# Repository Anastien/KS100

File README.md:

# KS100
KS100 is my take on entry level scientific calculators.

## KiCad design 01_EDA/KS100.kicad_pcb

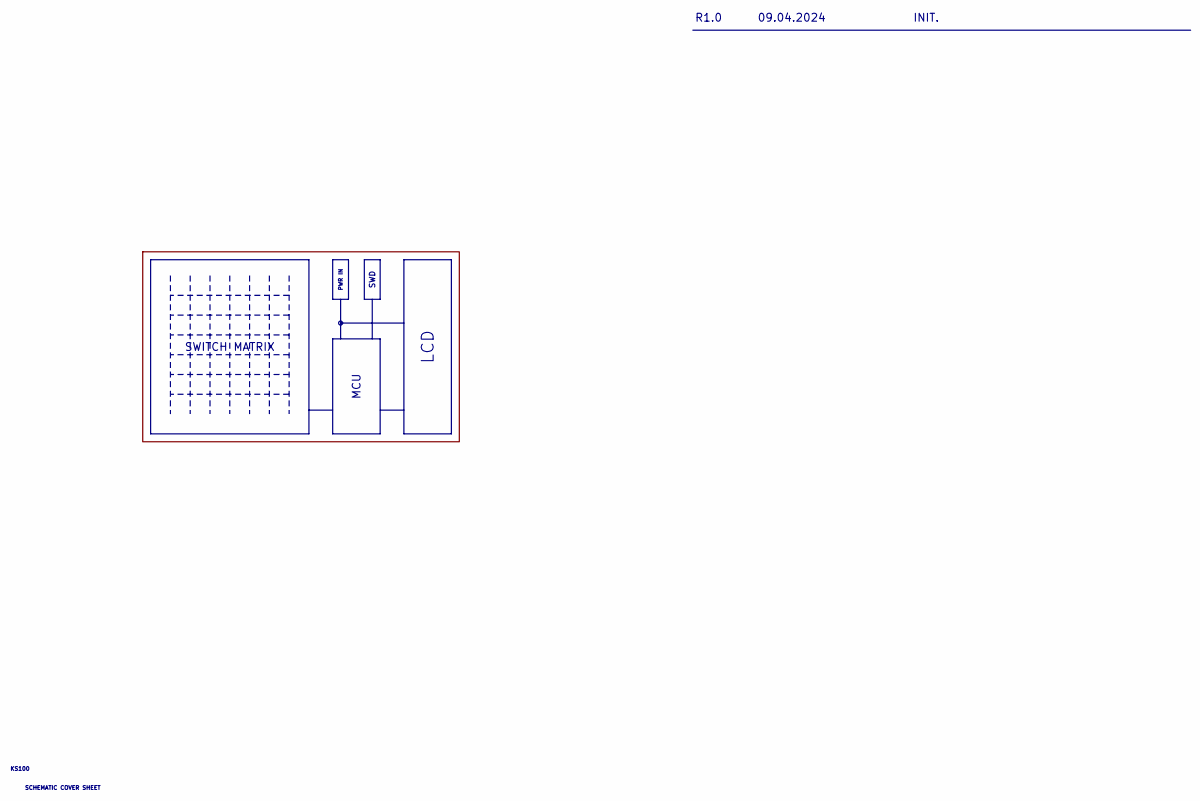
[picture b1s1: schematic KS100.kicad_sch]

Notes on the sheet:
R1.0
SCHEMATIC COVER SHEET
INIT.
09.04.2024
KS100
LCD
SWITCH MATRIX
SWD
MCU
PWR IN

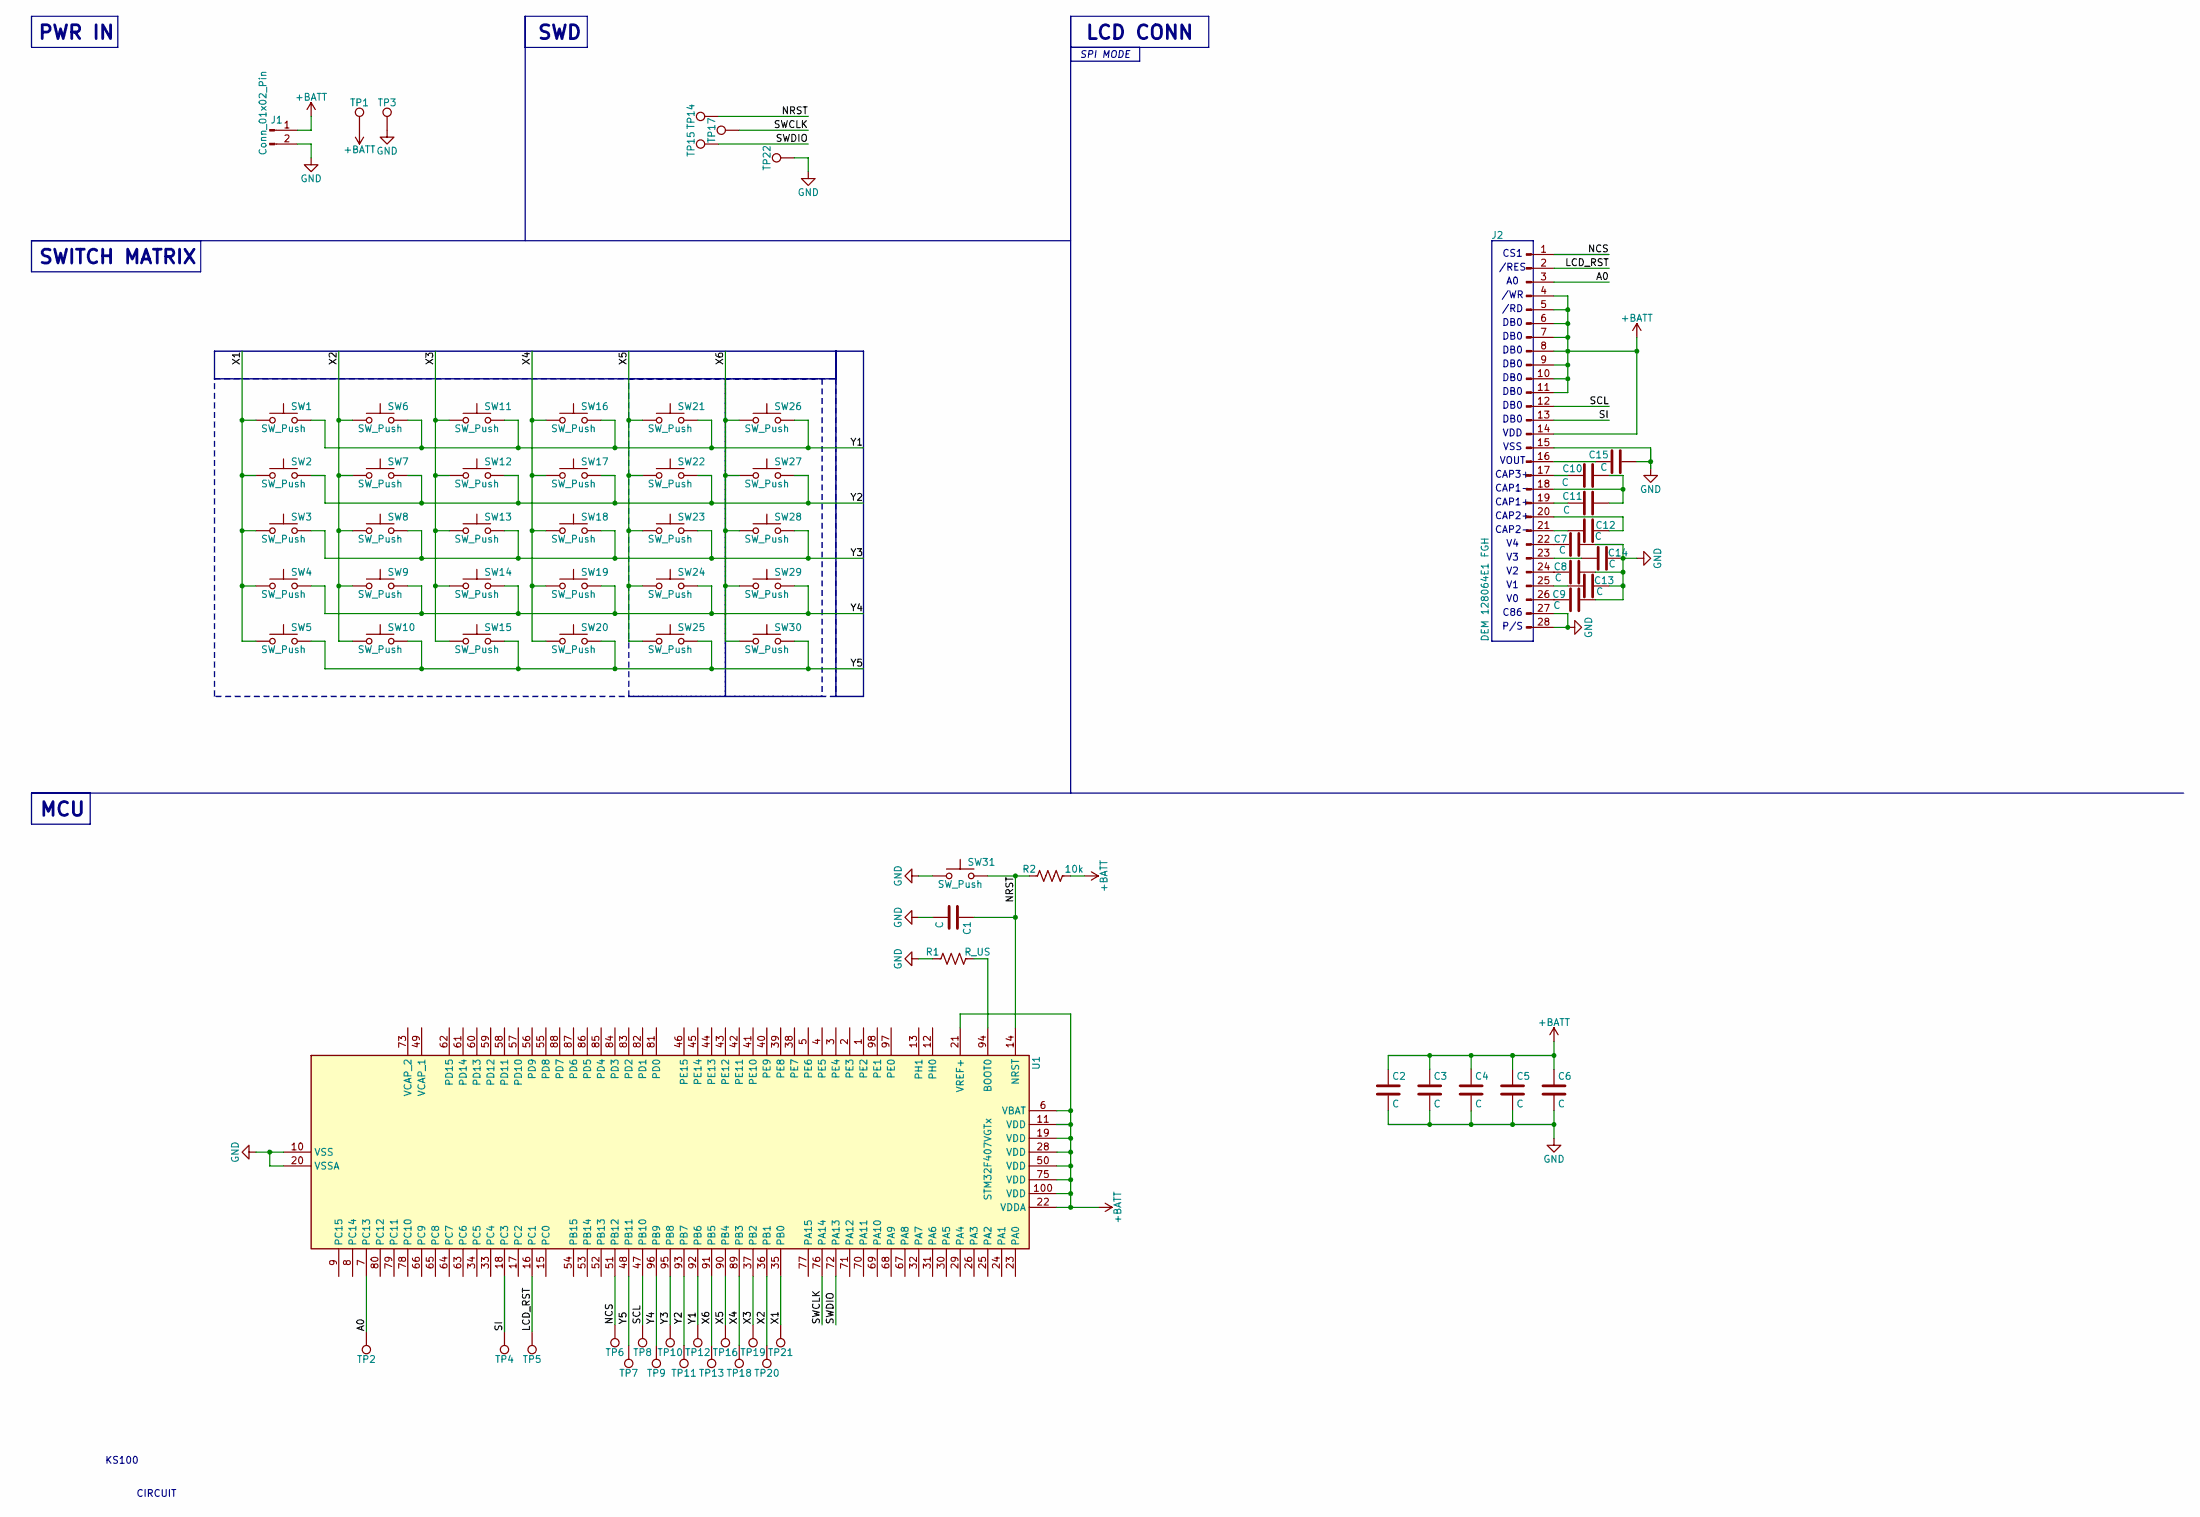
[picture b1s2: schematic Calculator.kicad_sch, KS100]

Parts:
C1, C2, C3, C4, C5, C6, C7, C8, C9, C10, C11, C12, C13, C14, C15: C; C_0603_1608Metric_Pad1.08x0.95mm_HandSolder
J1: Conn_01x02_Pin; JST_VH_B2P-VH-B_1x02_P3.96mm_Vertical
J2: DEM 128064E1 FGH
R1: R_US; R_0603_1608Metric_Pad0.98x0.95mm_HandSolder
R2: 10k; R_0603_1608Metric_Pad0.98x0.95mm_HandSolder
SW1, SW2, SW3, SW4, SW5, SW6, SW7, SW8, SW9, SW10, SW11, SW12, SW13, SW14, SW15, SW16, SW17, SW18, SW19, SW20, SW21, SW22, SW23, SW24, SW25, SW26, SW27, SW28, SW29, SW30, SW31: SW_Push; SW_PUSH_1P1T_6x3.5mm_H4.3_APEM_MJTP1243
TP1, TP2, TP3, TP4, TP5, TP6, TP7, TP8, TP9, TP10, TP11, TP12, TP13, TP16, TP18, TP19, TP20, TP21: TestPoint; TestPoint_THTPad_1.0x1.0mm_Drill0.5mm
TP14, TP15, TP17, TP22: TestPoint; TestPoint_THTPad_2.0x2.0mm_Drill1.0mm
U1: STM32F407VGTx; LQFP-100_14x14mm_P0.5mm

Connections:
+BATT: C2.1, C3.1, C4.1, C5.1, C6.1, J1.1, J2.4, J2.5, J2.6, J2.7, J2.8, J2.9, J2.10, J2.11, J2.14, R2.1, TP1.1, U1.6 (VBAT), U1.11 (VDD), U1.19 (VDD), U1.21 (VREF+), U1.22 (VDDA), U1.28 (VDD), U1.50 (VDD), U1.75 (VDD), U1.100 (VDD)
/Calculator/A0: J2.3, TP2.1, U1.7 (PC13)
/Calculator/LCD_RST: J2.2, TP5.1, U1.16 (PC1)
/Calculator/NCS: J2.1, TP6.1, U1.51 (PB12)
/Calculator/NRST: C1.1, R2.2, SW31.2, TP14.1, U1.14 (NRST)
/Calculator/SCL: J2.12, TP8.1, U1.47 (PB10)
/Calculator/SI: J2.13, TP4.1, U1.18 (PC3)
/Calculator/SWCLK: TP17.1, U1.76 (PA14)
/Calculator/SWDIO: TP15.1, U1.72 (PA13)
/Calculator/X1: SW1.1, SW2.1, SW3.1, SW4.1, SW5.1, TP21.1, U1.35 (PB0)
/Calculator/X2: SW6.1, SW7.1, SW8.1, SW9.1, SW10.1, TP20.1, U1.36 (PB1)
/Calculator/X3: SW11.1, SW12.1, SW13.1, SW14.1, SW15.1, TP19.1, U1.37 (PB2)
/Calculator/X4: SW16.1, SW17.1, SW18.1, SW19.1, SW20.1, TP18.1, U1.89 (PB3)
/Calculator/X5: SW21.1, SW22.1, SW23.1, SW24.1, SW25.1, TP16.1, U1.90 (PB4)
/Calculator/X6: SW26.1, SW27.1, SW28.1, SW29.1, SW30.1, TP13.1, U1.91 (PB5)
/Calculator/Y1: SW1.2, SW6.2, SW11.2, SW16.2, SW21.2, SW26.2, TP12.1, U1.92 (PB6)
/Calculator/Y2: SW2.2, SW7.2, SW12.2, SW17.2, SW22.2, SW27.2, TP11.1, U1.93 (PB7)
/Calculator/Y3: SW3.2, SW8.2, SW13.2, SW18.2, SW23.2, SW28.2, TP10.1, U1.95 (PB8)
/Calculator/Y4: SW4.2, SW9.2, SW14.2, SW19.2, SW24.2, SW29.2, TP9.1, U1.96 (PB9)
/Calculator/Y5: SW5.2, SW10.2, SW15.2, SW20.2, SW25.2, SW30.2, TP7.1, U1.48 (PB11)
GND: C1.2, C2.2, C3.2, C4.2, C5.2, C6.2, C7.2, C8.2, C9.2, C13.2, C14.2, C15.2, J1.2, J2.15, J2.27, J2.28, R1.2, SW31.1, TP3.1, TP22.1, U1.10 (VSS), U1.20 (VSSA), U1.27 (VSS), U1.74 (VSS), U1.99 (VSS)
unnamed: C15.1, J2.16
unnamed: C10.1, J2.17
unnamed: C10.2, C11.2, J2.18
unnamed: C11.1, J2.19
unnamed: C12.2, J2.20
unnamed: C12.1, J2.21
unnamed: C7.1, J2.22
unnamed: C14.1, J2.23
unnamed: C8.1, J2.24
unnamed: C13.1, J2.25
unnamed: C9.1, J2.26
unnamed: R1.1, U1.94 (BOOT0)

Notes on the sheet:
DB0
CAP3+
CAP2+
/RES
KS100
CIRCUIT
P/S
CS1
MCU
/WR
CAP2-
LCD CONN
CAP1+
VSS
VOUT
VDD
CAP1-
SWITCH MATRIX
SWD
/RD
C86
PWR IN
SPI MODE

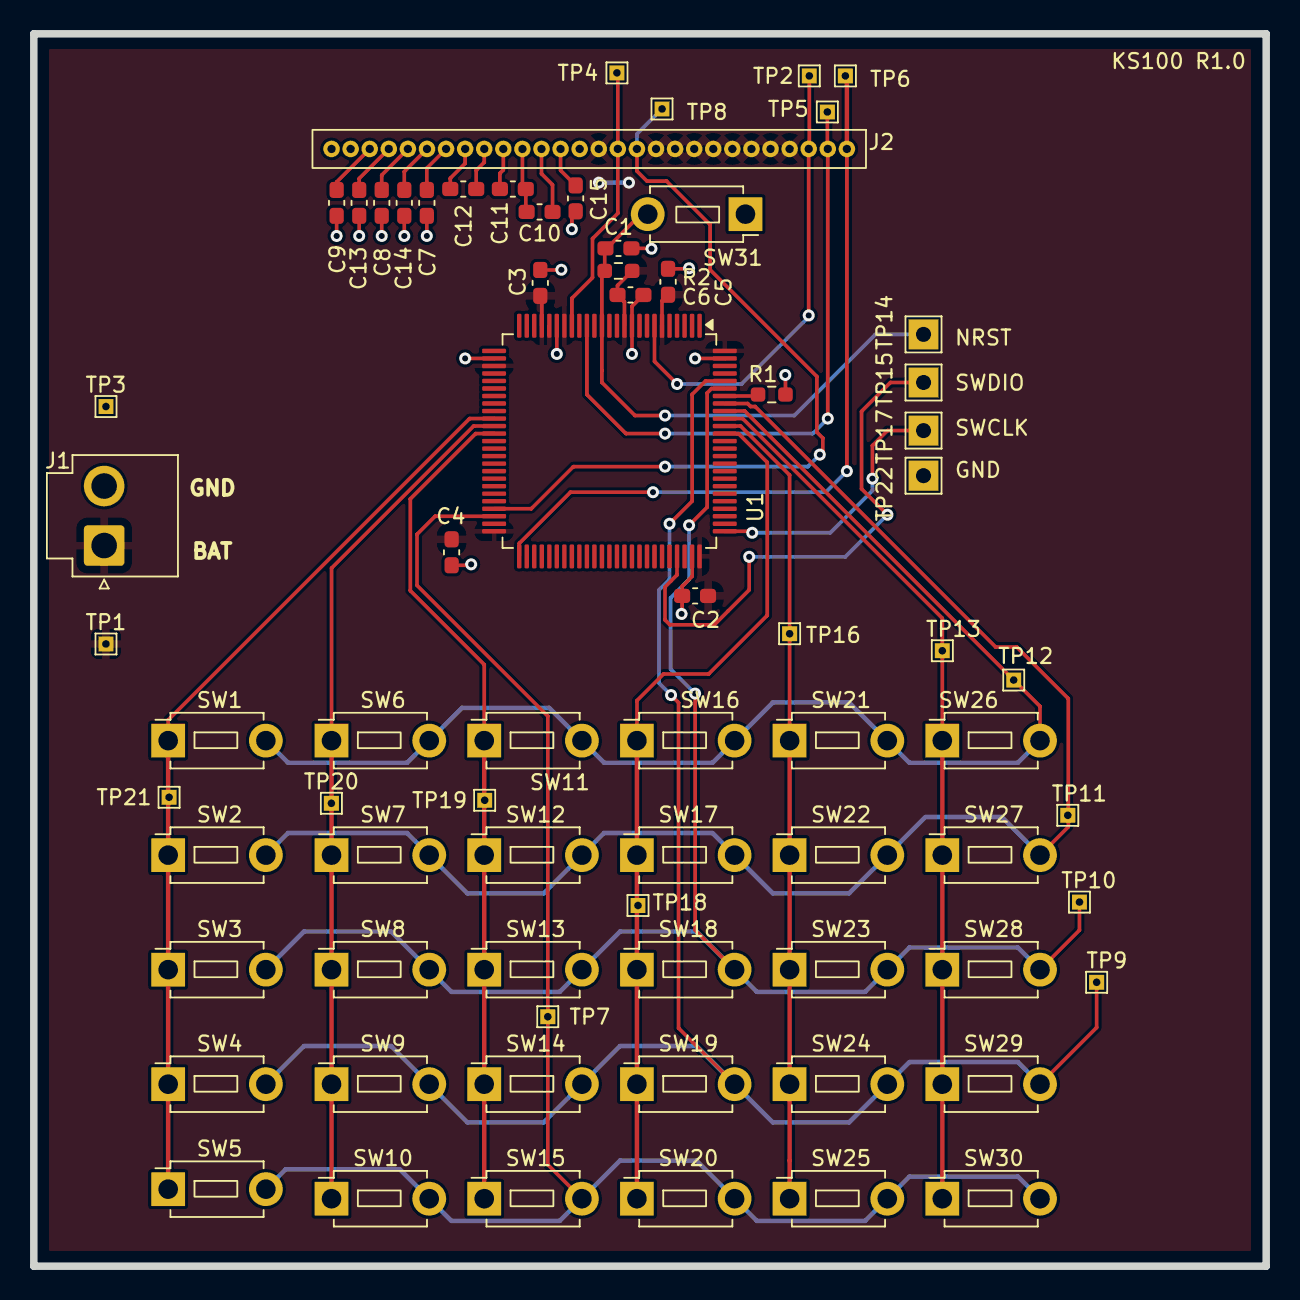
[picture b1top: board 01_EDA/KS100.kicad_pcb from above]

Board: 2 copper layers, 82.0 x 82.0 mm, 73 parts (0 on the bottom side), 33 nets.

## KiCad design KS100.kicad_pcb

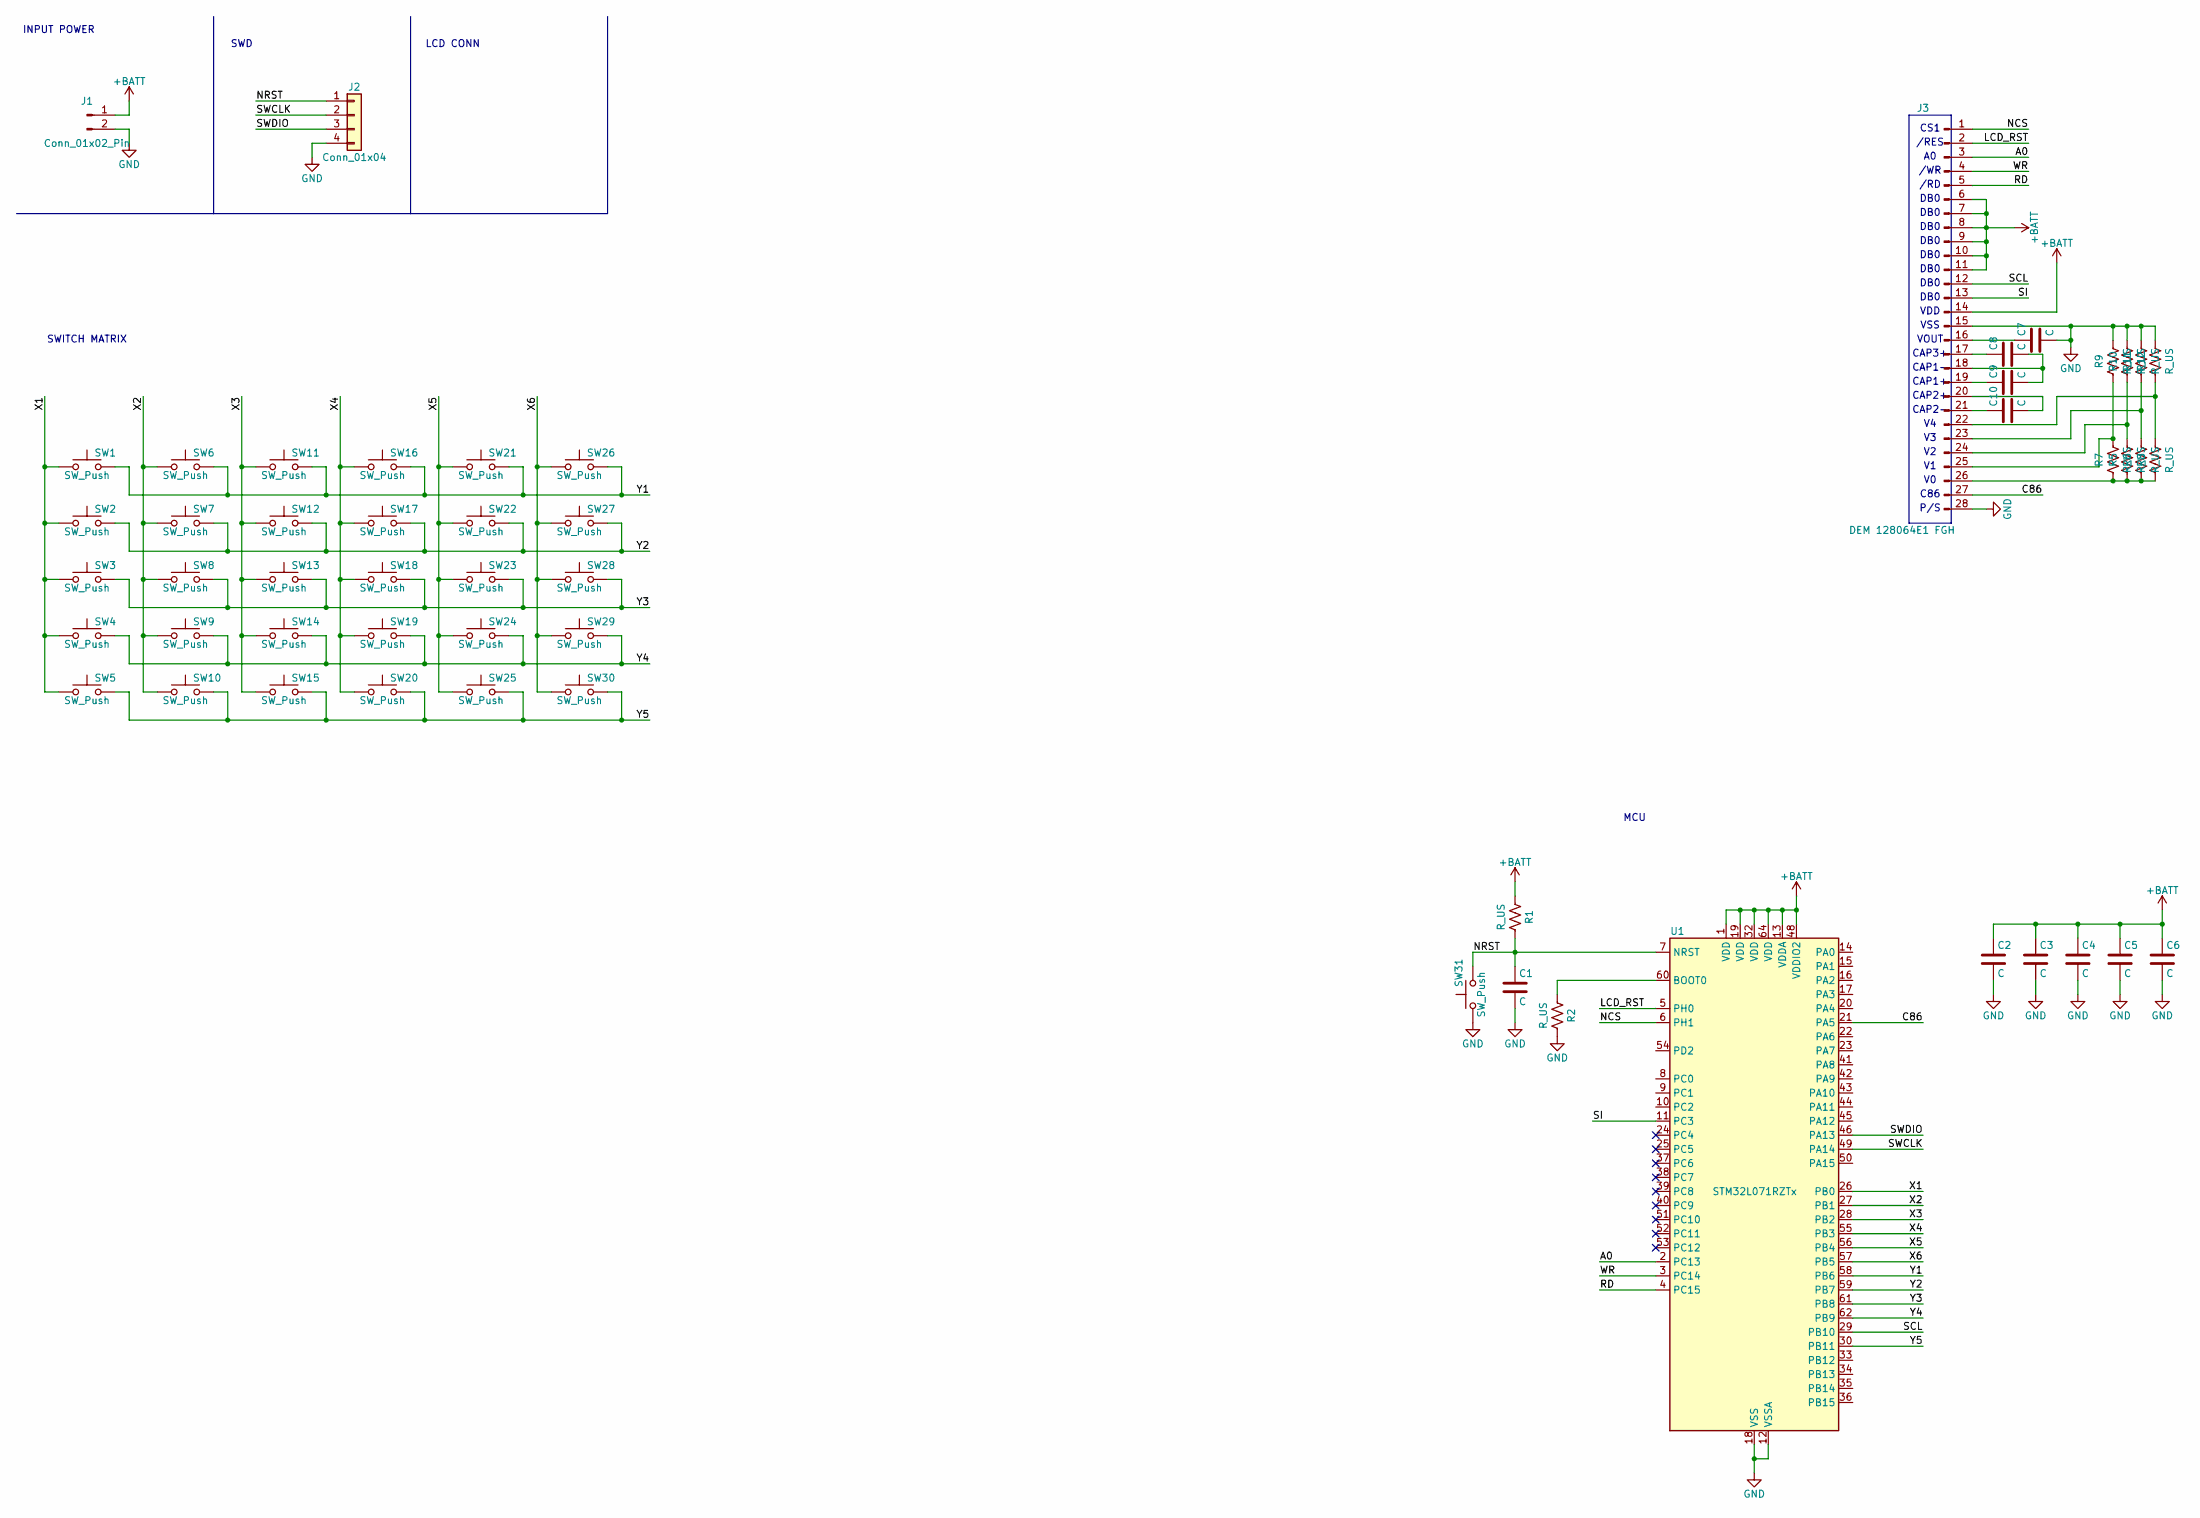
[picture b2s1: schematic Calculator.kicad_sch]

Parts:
C1, C2, C3, C4, C5, C6, C7, C8, C9, C10: C; C_0603_1608Metric_Pad1.08x0.95mm_HandSolder
J1: Conn_01x02_Pin; PinHeader_1x02_P2.00mm_Vertical
J2: Conn_01x04; PinHeader_1x04_P1.00mm_Vertical
J3: DEM 128064E1 FGH
R1, R2, R5, R6, R7, R8, R9, R10, R11, R12: R_US; R_0603_1608Metric_Pad0.98x0.95mm_HandSolder
SW1, SW2, SW3, SW4, SW5, SW6, SW7, SW8, SW9, SW10, SW11, SW12, SW13, SW14, SW15, SW16, SW17, SW18, SW19, SW20, SW21, SW22, SW23, SW24, SW25, SW26, SW27, SW28, SW29, SW30, SW31: SW_Push; SW_PUSH_1P1T_6x3.5mm_H4.3_APEM_MJTP1243
U1: STM32L071RZTx; LQFP-64_10x10mm_P0.5mm

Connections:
+BATT: C2.1, C3.1, C4.1, C5.1, C6.1, J1.1, J3.6, J3.7, J3.8, J3.9, J3.10, J3.11, J3.14, R1.1, U1.1 (VDD), U1.13 (VDDA), U1.19 (VDD), U1.32 (VDD), U1.48 (VDDIO2), U1.64 (VDD)
/Calculator/A0: J3.3, U1.2 (PC13)
/Calculator/C86: J3.27, U1.21 (PA5)
/Calculator/LCD_RST: J3.2, U1.5 (PH0)
/Calculator/NCS: J3.1, U1.6 (PH1)
/Calculator/NRST: C1.1, J2.1, R1.2, SW31.2, U1.7 (NRST)
/Calculator/RD: J3.5, U1.4 (PC15)
/Calculator/SCL: J3.12, U1.29 (PB10)
/Calculator/SI: J3.13, U1.11 (PC3)
/Calculator/SWCLK: J2.2, U1.49 (PA14)
/Calculator/SWDIO: J2.3, U1.46 (PA13)
/Calculator/WR: J3.4, U1.3 (PC14)
/Calculator/X1: SW1.1, SW2.1, SW3.1, SW4.1, SW5.1, U1.26 (PB0)
/Calculator/X2: SW6.1, SW7.1, SW8.1, SW9.1, SW10.1, U1.27 (PB1)
/Calculator/X3: SW11.1, SW12.1, SW13.1, SW14.1, SW15.1, U1.28 (PB2)
/Calculator/X4: SW16.1, SW17.1, SW18.1, SW19.1, SW20.1, U1.55 (PB3)
/Calculator/X5: SW21.1, SW22.1, SW23.1, SW24.1, SW25.1, U1.56 (PB4)
/Calculator/X6: SW26.1, SW27.1, SW28.1, SW29.1, SW30.1, U1.57 (PB5)
/Calculator/Y1: SW1.2, SW6.2, SW11.2, SW16.2, SW21.2, SW26.2, U1.58 (PB6)
/Calculator/Y2: SW2.2, SW7.2, SW12.2, SW17.2, SW22.2, SW27.2, U1.59 (PB7)
/Calculator/Y3: SW3.2, SW8.2, SW13.2, SW18.2, SW23.2, SW28.2, U1.61 (PB8)
/Calculator/Y4: SW4.2, SW9.2, SW14.2, SW19.2, SW24.2, SW29.2, U1.62 (PB9)
/Calculator/Y5: SW5.2, SW10.2, SW15.2, SW20.2, SW25.2, SW30.2, U1.30 (PB11)
GND: C1.2, C2.2, C3.2, C4.2, C5.2, C6.2, C7.2, J1.2, J2.4, J3.15, J3.28, R2.2, R9.2, R10.2, R11.2, R12.2, SW31.1, U1.12 (VSSA), U1.18 (VSS), U1.31 (VSS), U1.47 (VSS), U1.63 (VSS)
unnamed: C7.1, J3.16
unnamed: C8.1, J3.17
unnamed: C8.2, C9.2, J3.18
unnamed: C9.1, J3.19
unnamed: C10.2, J3.20
unnamed: C10.1, J3.21
unnamed: J3.22, R8.2, R12.1
unnamed: J3.23, R6.2, R11.1
unnamed: J3.24, R5.2, R10.1
unnamed: J3.25, R7.2, R9.1
unnamed: J3.26, R5.1, R6.1, R7.1, R8.1
unnamed: R2.1, U1.60 (BOOT0)

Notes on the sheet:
LCD CONN
DB0
INPUT POWER
CAP3+
CAP2+
/RES
P/S
CS1
/WR
CAP2-
SWD
CAP1+
VSS
VOUT
VDD
CAP1-
SWITCH MATRIX
/RD
C86
MCU

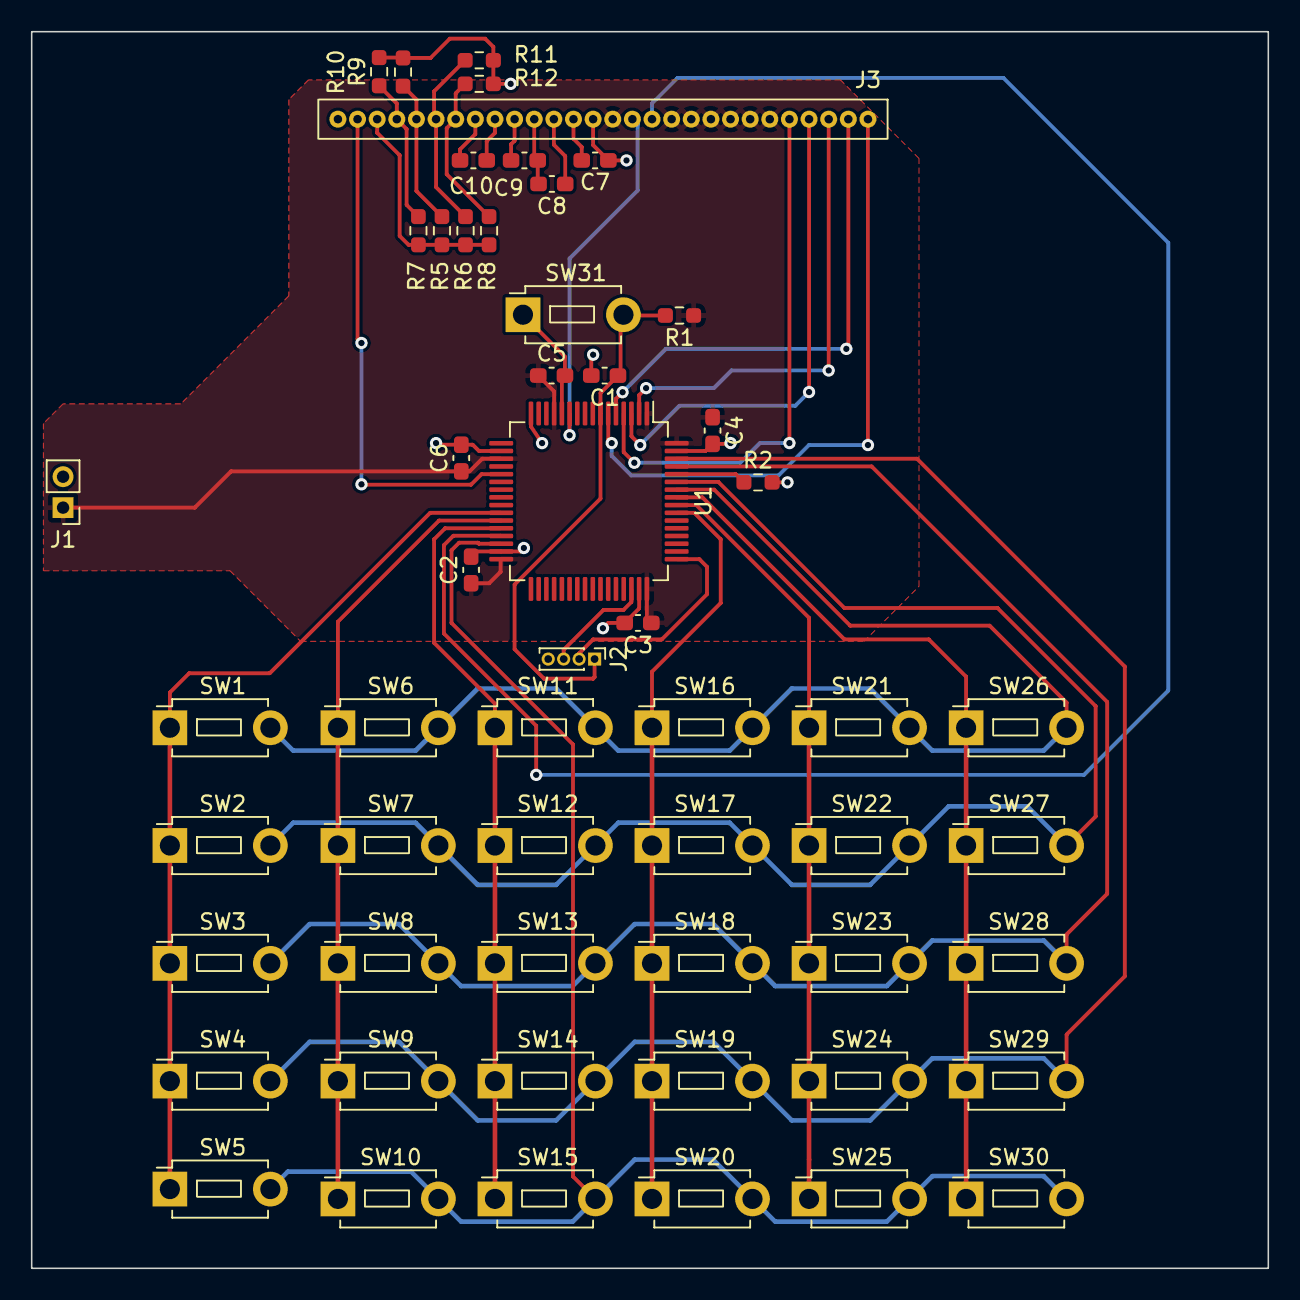
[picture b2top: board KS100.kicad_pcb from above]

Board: 2 copper layers, 80.0 x 80.0 mm, 55 parts (0 on the bottom side), 36 nets.

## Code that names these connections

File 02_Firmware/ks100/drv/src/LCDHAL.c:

/*
 * lcd.c
 *
 *  Created on: Mar 20, 2024
 *      Author: anast
 */
/* HW Interface
 * RESET , Active Low	-> PC1
 * SPI
 * CS					-> PB12
 * SCL					-> PB10
 * SI					-> PC3
 */





#include <LCDHAL.h>
#include "stm32f407xx.h"
#include "stm32f407xx_gpio.h"
#include "stm32f407xx_spi.h"
#include "DEM128064E1FGH.h"

// LCD Init
void LCD_Init()
{
	//Control GPIO

	GPIO_Handel_t LCD_Pin;
	//RST
	LCD_Pin.pGPIOX = GPIOC;
	LCD_Pin.GPIO_PinConfig.GPIO_PinNumber = GPIO_PI_NO_1;
	LCD_Pin.GPIO_PinConfig.GPIO_PinOPType= GPIO_TYPE_PP;
	LCD_Pin.GPIO_PinConfig.GPIO_PinMode = GPIO_MODE_OUT;
	GPIO_Init(&LCD_Pin);
	GPIO_WriteToOutputPin(GPIOC, GPIO_PI_NO_1, 1);

	//A0
	LCD_Pin.pGPIOX = GPIOC;
	LCD_Pin.GPIO_PinConfig.GPIO_PinNumber = GPIO_PI_NO_13;
	GPIO_Init(&LCD_Pin);
	GPIO_WriteToOutputPin(GPIOC, GPIO_PI_NO_13, 0);

	//SPI_GPIO
	GPIO_Handel_t SPI2_PIN;
	SPI2_PIN.pGPIOX = GPIOC;
	SPI2_PIN.GPIO_PinConfig.GPIO_PinMode = GPIO_MODE_ALTFN;
	SPI2_PIN.GPIO_PinConfig.GPIO_PinAltFunMode=5;
	SPI2_PIN.GPIO_PinConfig.GPIO_PinOPType= GPIO_TYPE_PP;

	//spi2 MOSI
	SPI2_PIN.GPIO_PinConfig.GPIO_PinNumber = GPIO_PI_NO_3;
	GPIO_Init(&SPI2_PIN);

	//spi2 SCL
	SPI2_PIN.pGPIOX = GPIOB;
	SPI2_PIN.GPIO_PinConfig.GPIO_PinMode = GPIO_MODE_ALTFN;
	SPI2_PIN.GPIO_PinConfig.GPIO_PinAltFunMode=5;
	SPI2_PIN.GPIO_PinConfig.GPIO_PinOPType= GPIO_TYPE_PP;
	//SPI2_PIN.GPIO_PinConfig.GPIO_PiPuPdControl = GPIO_PIN_PU;
	SPI2_PIN.GPIO_PinConfig.GPIO_PinNumber = GPIO_PI_NO_10;
	GPIO_Init(&SPI2_PIN);

	//CS
	SPI2_PIN.pGPIOX = GPIOB;
	SPI2_PIN.GPIO_PinConfig.GPIO_PinMode = GPIO_MODE_ALTFN;
	SPI2_PIN.GPIO_PinConfig.GPIO_PinAltFunMode=5;
	SPI2_PIN.GPIO_PinConfig.GPIO_PinOPType= GPIO_TYPE_PP;
	SPI2_PIN.GPIO_PinConfig.GPIO_PinNumber = GPIO_PI_NO_12;
	GPIO_Init(&SPI2_PIN);


	//SPI2
	SPI_Handel_t SPI2_h;
	SPI2_h.pSPIX = SPI2;
	SPI2_h.SPIConfig.SPI_BusConfig = SPI_S_TX;
	SPI2_h.SPIConfig.SPI_DeviceMode = SPI_MODE_MASTER;
	SPI2_h.SPIConfig.SPI_SclkSpeed = PCLK_D32;//781kHz
	SPI2_h.SPIConfig.SPI_DFF = SPI_DFF_8BITS;
	SPI2_h.SPIConfig.SPI_SSM = SPI_SSM_DI;
	SPI2_h.SPIConfig.SPI_CPHA = SPI_CPHA_SECOND_EDGE;
	SPI2_h.SPIConfig.SPI_CPOL = SPI_CPOL_HIGH;
	SPI2_h.SPIConfig.SPI_FF = SPI_MSB;
	SPIx_Init(&SPI2_h);




	//LCD Commands
	LCD_RST();
	LCD_Bias();
	LCD_ADC(ENABLE);
	LCD_ComMode();
	//LCD_StrtLineAddr(0x40);
	LCD_RbRa();
	delay(TIM6, 5);
	LCD_Evol();
	LCD_PwrConfig();
	LCD_BstMult();
	delay(TIM6, 5);
	LCD_Onoff(ENABLE);
	LCD_Normal(DISABLE);


}

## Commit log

2023-11-08 INIT.
2023-11-11 Update.
2024-04-15 adding firmware resources.
2024-04-15 Restructure.
